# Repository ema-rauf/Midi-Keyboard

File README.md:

# MIDI Keyboard

A USB MIDI controller on a custom PCB. Touch the copper keys to play notes, press the switches for drums, and turn the knob for volume.

It plugs into a computer over USB-C and shows up as a MIDI instrument, so it works with music software like FL Studio, Ableton or LMMS.

## How it works

The 7 piano keys are bare copper pads on the PCB. The ESP32-S3 measures their capacitance, so when your finger touches a pad it detects the change and sends a MIDI note. The 3 Choc switches send drum notes, the rotary encoder changes the computer's volume, and 3 RGB LEDs mounted on the back shine through holes in the board.

## Why I made it

I wanted to learn PCB design from start to finish: drawing a schematic, making a custom footprint, laying out and routing a board, and getting it ready to manufacture. A MIDI keypad was a fun way to do that, because at the end I get a real instrument I can make beats with.

## Features

- 7 capacitive touch keys (C major scale, MIDI notes 60-71)
- 3 Kailh Choc low-profile switches (kick, snare, hi-hat)
- 1 EC11 rotary encoder (computer volume)
- 3 SK6812MINI-E RGB LEDs, reverse-mounted to shine through the board
- Waveshare ESP32-S3-Zero, plugs in over USB-C

## Parts list

| Designator | Part | Qty | Cost (USD) |
|---|---|---|---|
| U1 | Waveshare ESP32-S3-Zero | 1 | 6.62 |
| SW1-SW3 | Kailh Choc low-profile switch | 3 | 6.04 |
| SW4 | EC11 rotary encoder (20 mm shaft, with switch) | 1 | 1.44 |
| D1-D3 | SK6812MINI-E RGB LED (reverse mount) | 3 | 3.36 |
| J1 | Capacitive touch keys (copper on the PCB) | 1 | 0.00 |
| PCB | 2-layer PCB from JLCPCB (5 pcs) | 1 | see quote |

Full list with links: [BOM.csv](BOM.csv)

## Pin map

| Part | Pins |
|---|---|
| Touch keys 1-7 | GP13, GP12, GP11, GP10, GP9, GP8, GP7 |
| Switches SW1-SW3 | GP4, GP5, GP6 |
| Encoder A / B | TX (GPIO43) / RX (GPIO44) |
| LED data | GP3 |
| LED power | 5V |

## Files

- `PCB/` KiCad project (schematic, board, custom touch-key footprint)
- `PCB/production/` Gerber zip, BOM and positions for JLCPCB
- `firmware/code.py` KMK firmware
- `BOM.csv` parts list with prices and links

## Firmware setup

1. Install CircuitPython for the Waveshare ESP32-S3-Zero.
2. Copy the `kmk` folder from [KMK](https://github.com/KMKfw/kmk_firmware) and the `adafruit_midi` library onto the board.
3. Copy `firmware/code.py` onto the board.
4. Don't touch the keys while it boots: the touch pads calibrate at startup.

## Credits

Based on [Kai Pereira's MIDI keypad tutorial](https://github.com/KaiPereira/MIDI-Keypad).

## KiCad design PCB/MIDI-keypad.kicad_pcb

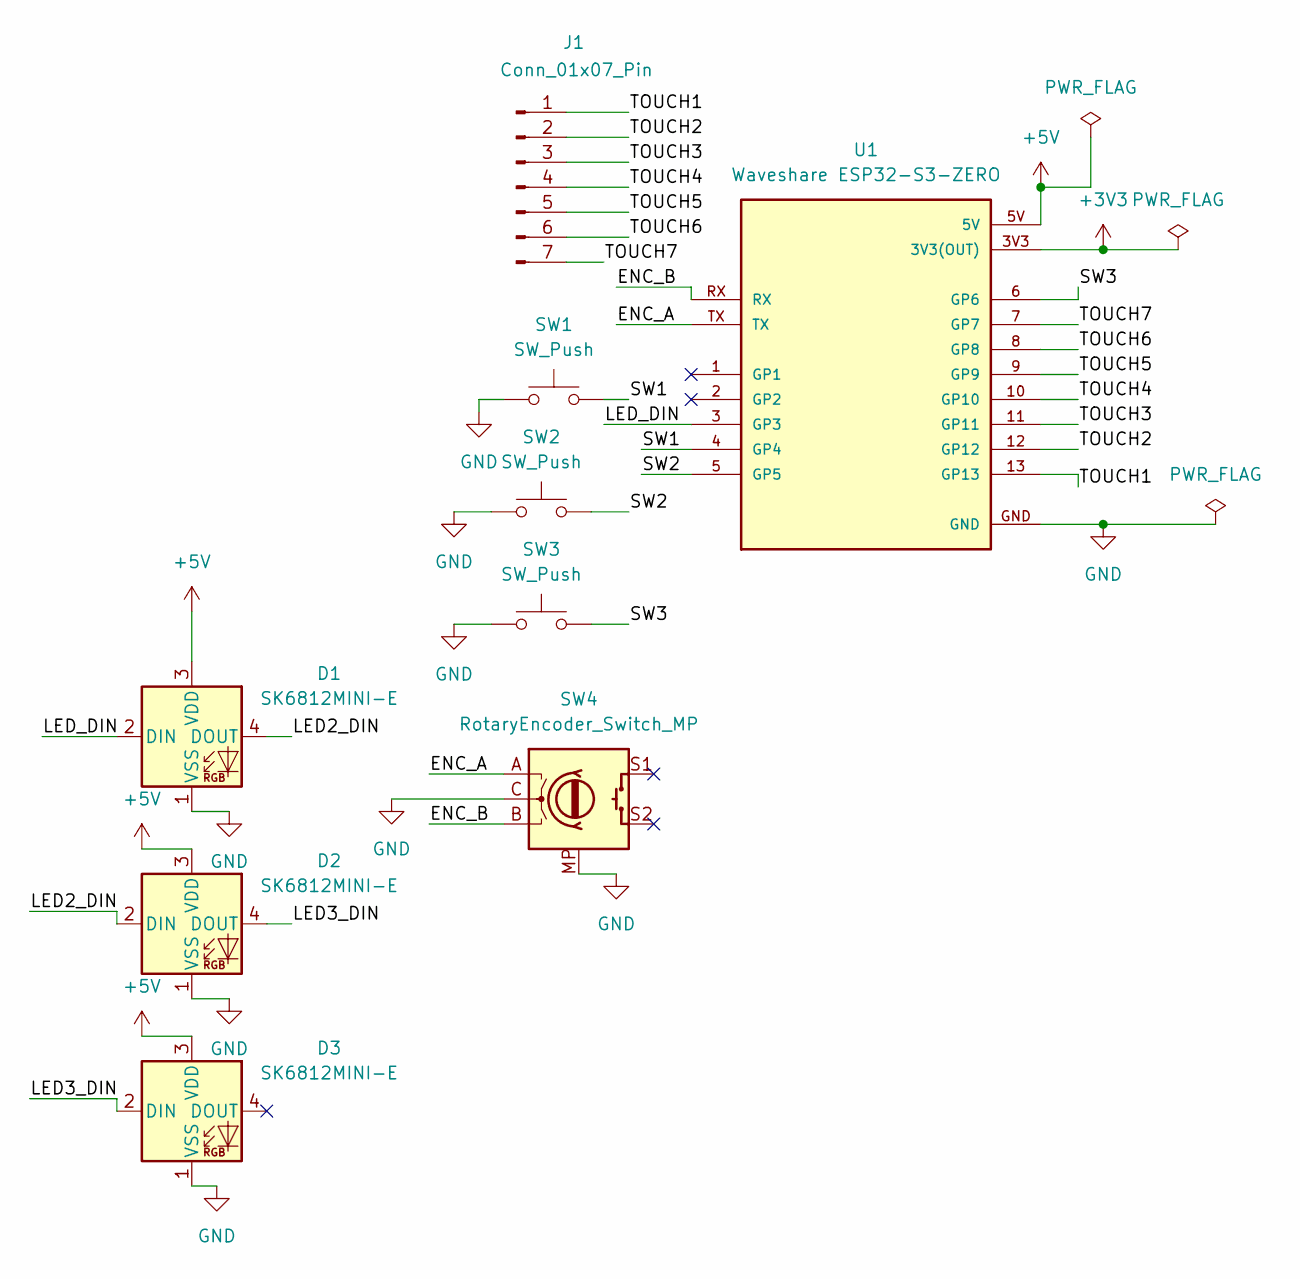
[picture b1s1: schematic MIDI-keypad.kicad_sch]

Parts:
D1, D2, D3: SK6812MINI-E; LED_SK6812MINI-E_3.2x2.8mm_P1.5mm_ReverseMount
J1: Conn_01x07_Pin; Capacitive Keys
SW1, SW2, SW3: SW_Push; Kailh Choc Low-Profile Switches
SW4: RotaryEncoder_Switch_MP; RotaryEncoder_Alps_EC11E-Switch_Vertical_H20mm
U1: Waveshare ESP32-S3-ZERO; Waveshare ESP32-S3-Zero; PARTREV NA

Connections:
+3V3: U1.3V3 (3V3(OUT))
+5V: D1.3 (VDD), D2.3 (VDD), D3.3 (VDD), U1.5V
/ENC_A: SW4.A, U1.TX
/ENC_B: SW4.B, U1.RX
/LED2_DIN: D1.4 (DOUT), D2.2 (DIN)
/LED3_DIN: D2.4 (DOUT), D3.2 (DIN)
/LED_DIN: D1.2 (DIN), U1.3 (GP3)
/SW1: SW1.2, U1.4 (GP4)
/SW2: SW2.2, U1.5 (GP5)
/SW3: SW3.2, U1.6 (GP6)
/TOUCH1: J1.1, U1.13 (GP13)
/TOUCH2: J1.2, U1.12 (GP12)
/TOUCH3: J1.3, U1.11 (GP11)
/TOUCH4: J1.4, U1.10 (GP10)
/TOUCH5: J1.5, U1.9 (GP9)
/TOUCH6: J1.6, U1.8 (GP8)
/TOUCH7: J1.7, U1.7 (GP7)
GND: D1.1 (VSS), D2.1 (VSS), D3.1 (VSS), SW1.1, SW2.1, SW3.1, SW4.C, SW4.MP, U1.GND

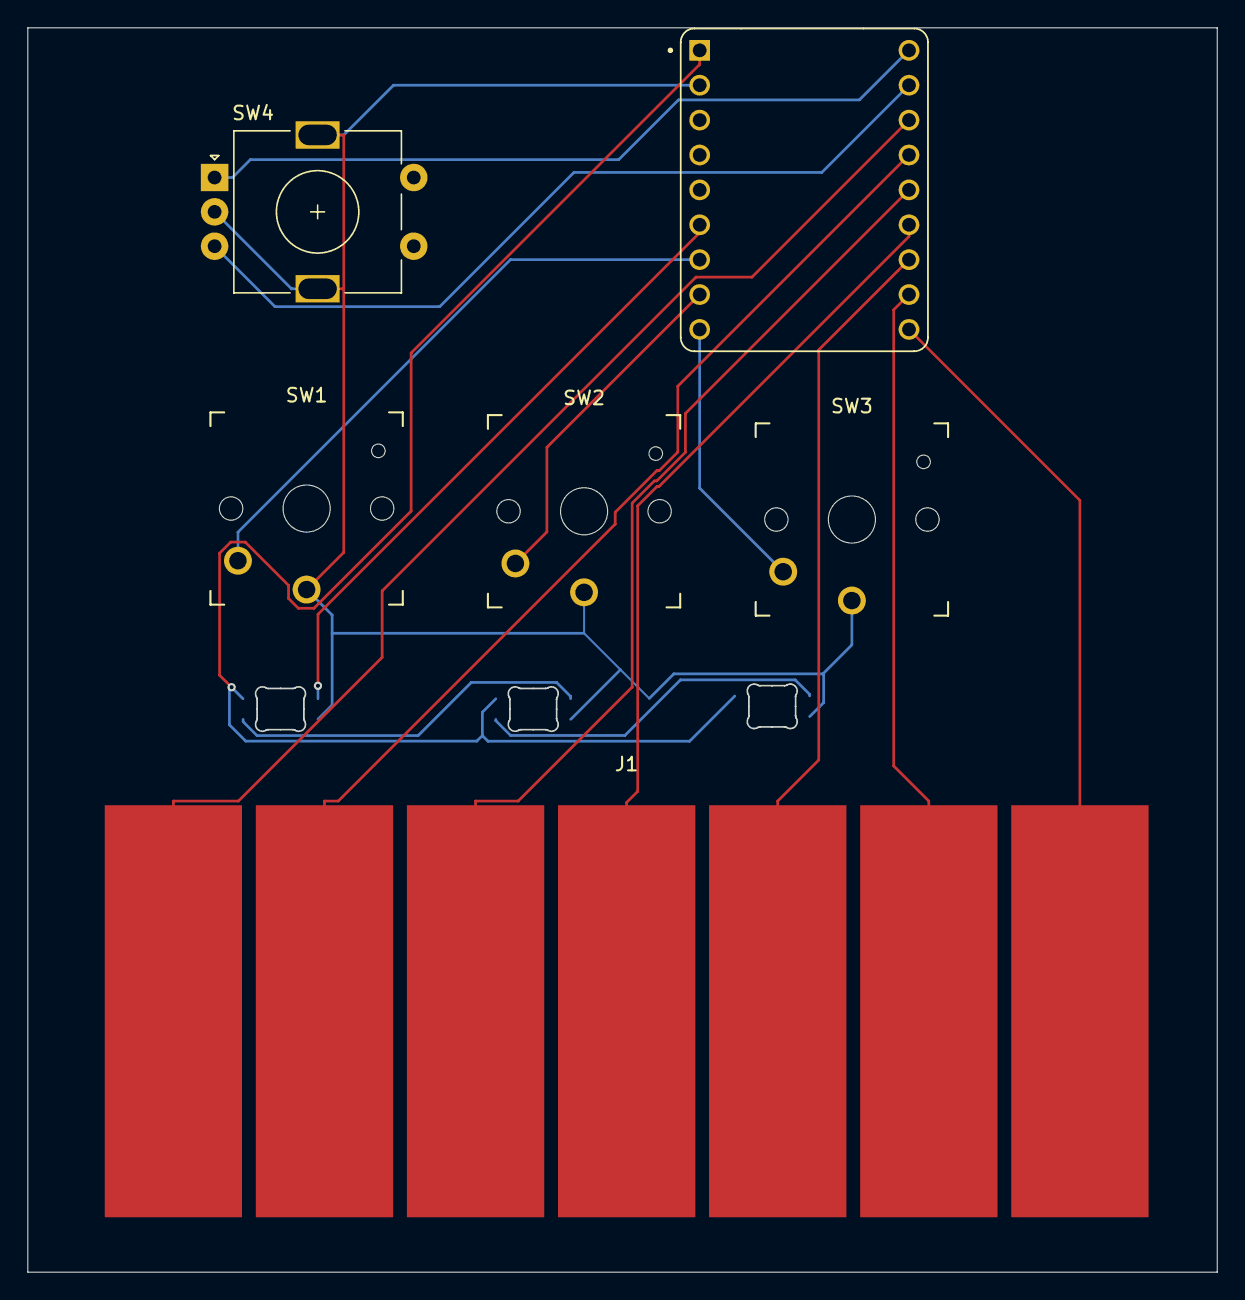
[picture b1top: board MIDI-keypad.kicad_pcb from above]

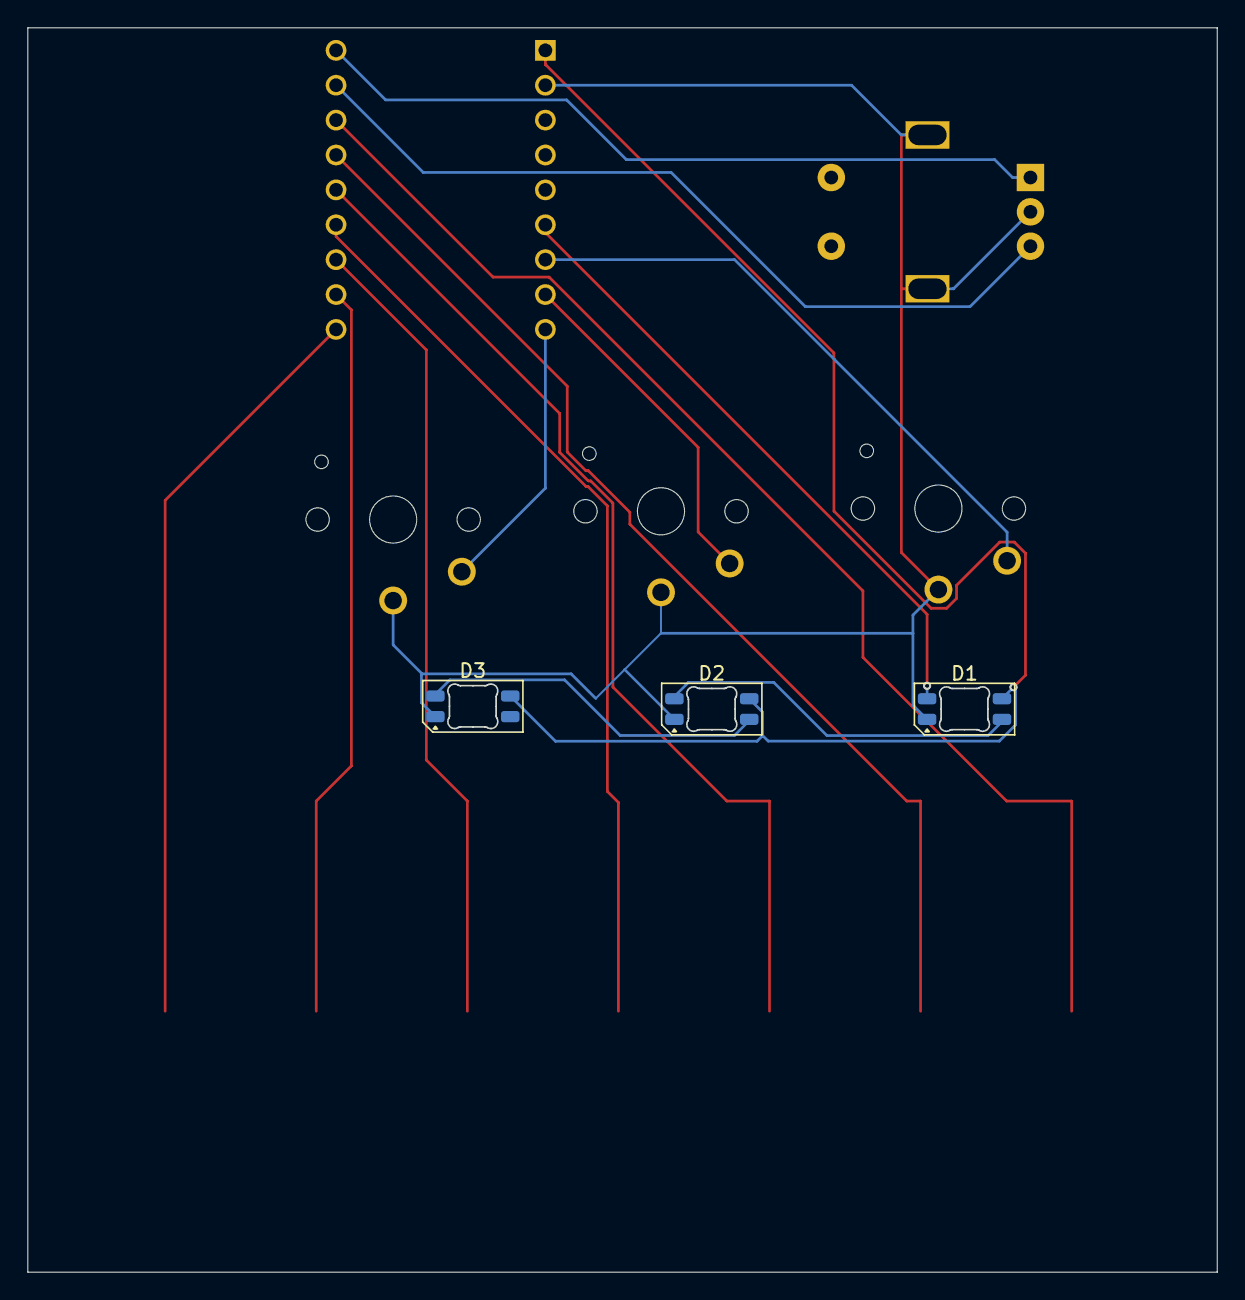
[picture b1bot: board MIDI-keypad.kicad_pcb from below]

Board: 2 copper layers, 86.6 x 90.6 mm, 9 parts (3 on the bottom side), 17 nets.

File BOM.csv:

Designator,Part,Footprint,Quantity,Total Cost (USD),Link
U1,Waveshare ESP32-S3-Zero,Waveshare ESP32-S3-Zero,1,6.62,https://www.aliexpress.com/item/1005007004089798.html
"SW1, SW2, SW3",Kailh Choc Low-Profile Switch,Kailh Choc Low-Profile Switches,3,6.04,https://www.aliexpress.com/item/1005008883418065.html
SW4,EC11 Rotary Encoder,RotaryEncoder_Alps_EC11E-Switch_Vertical_H20mm,1,1.44,https://www.aliexpress.com/item/1005007644083514.html
"D1, D2, D3",SK6812MINI-E RGB LED,LED_SK6812MINI-E_3.2x2.8mm_P1.5mm_ReverseMount,3,3.36,https://www.aliexpress.com/item/1005007863635868.html
J1,Capacitive touch keys (PCB copper),Capacitive Keys,1,0.00,
PCB,2-layer PCB from JLCPCB (5 pcs),,1,FILL_FROM_QUOTE,https://jlcpcb.com/
